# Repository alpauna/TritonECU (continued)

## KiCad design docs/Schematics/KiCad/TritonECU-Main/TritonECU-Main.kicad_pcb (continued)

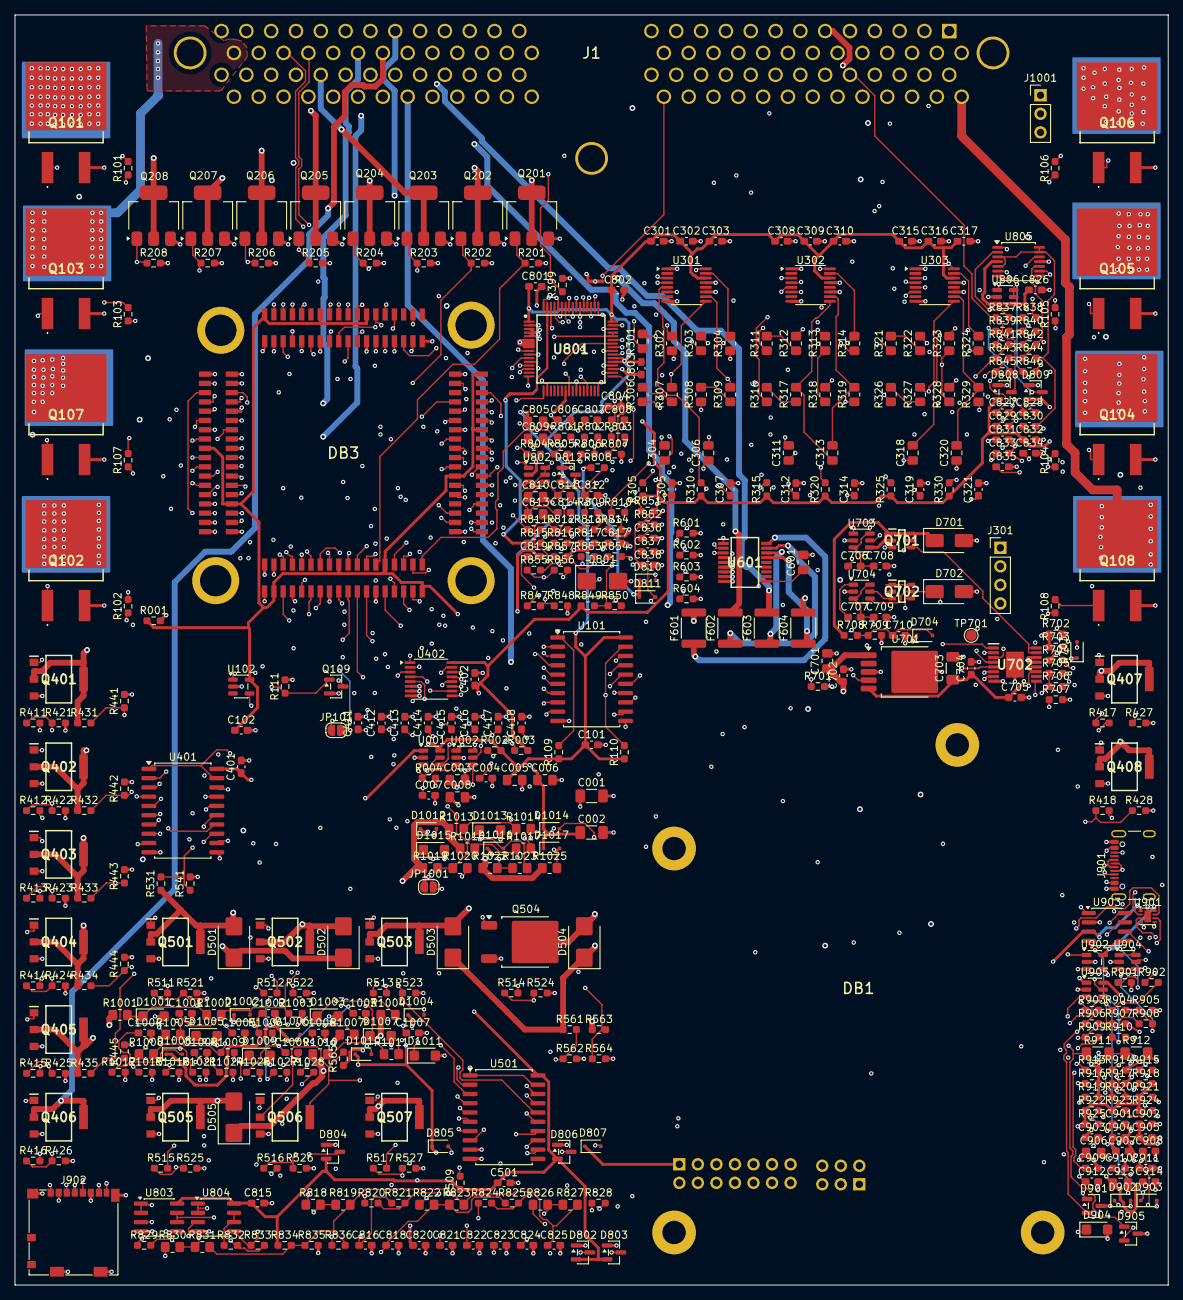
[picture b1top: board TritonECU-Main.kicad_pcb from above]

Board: 6 copper layers, 158.0 x 174.0 mm, 457 parts (0 on the bottom side), 358 nets.

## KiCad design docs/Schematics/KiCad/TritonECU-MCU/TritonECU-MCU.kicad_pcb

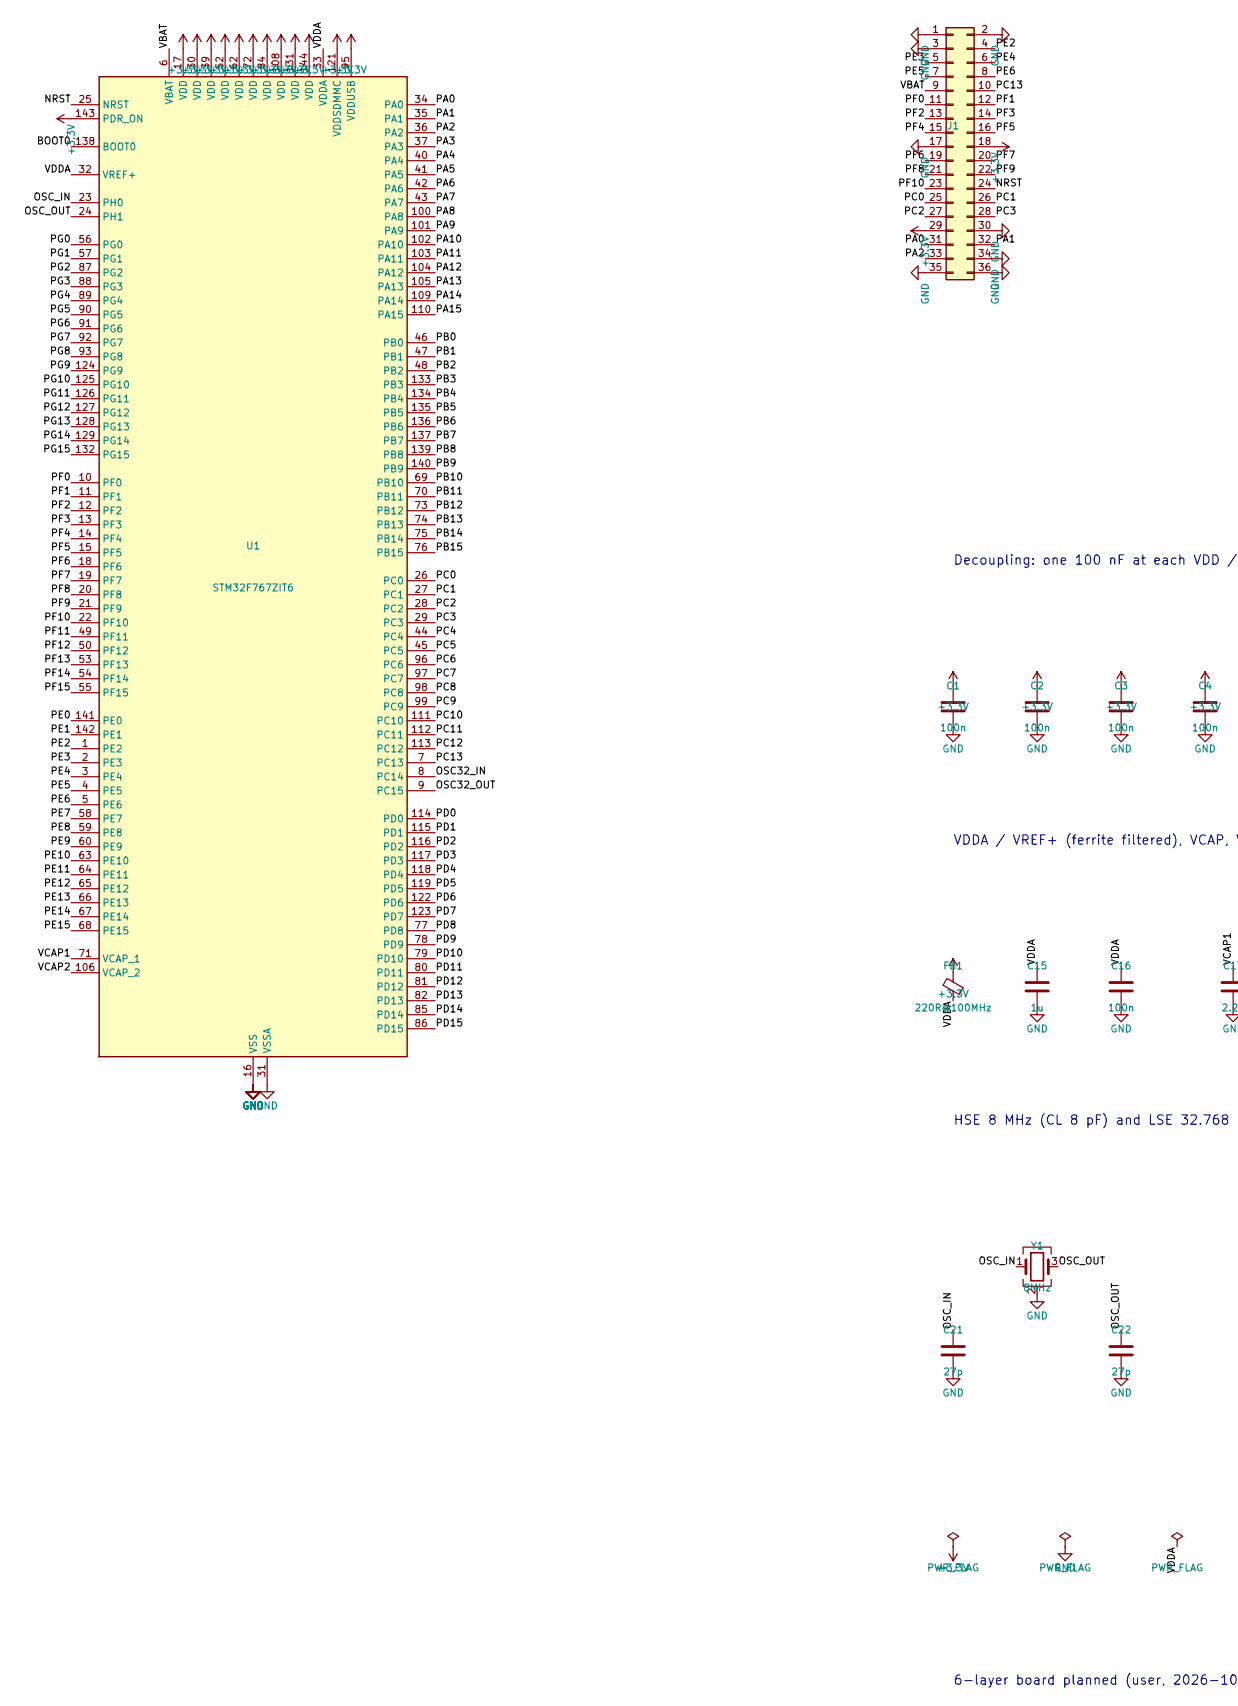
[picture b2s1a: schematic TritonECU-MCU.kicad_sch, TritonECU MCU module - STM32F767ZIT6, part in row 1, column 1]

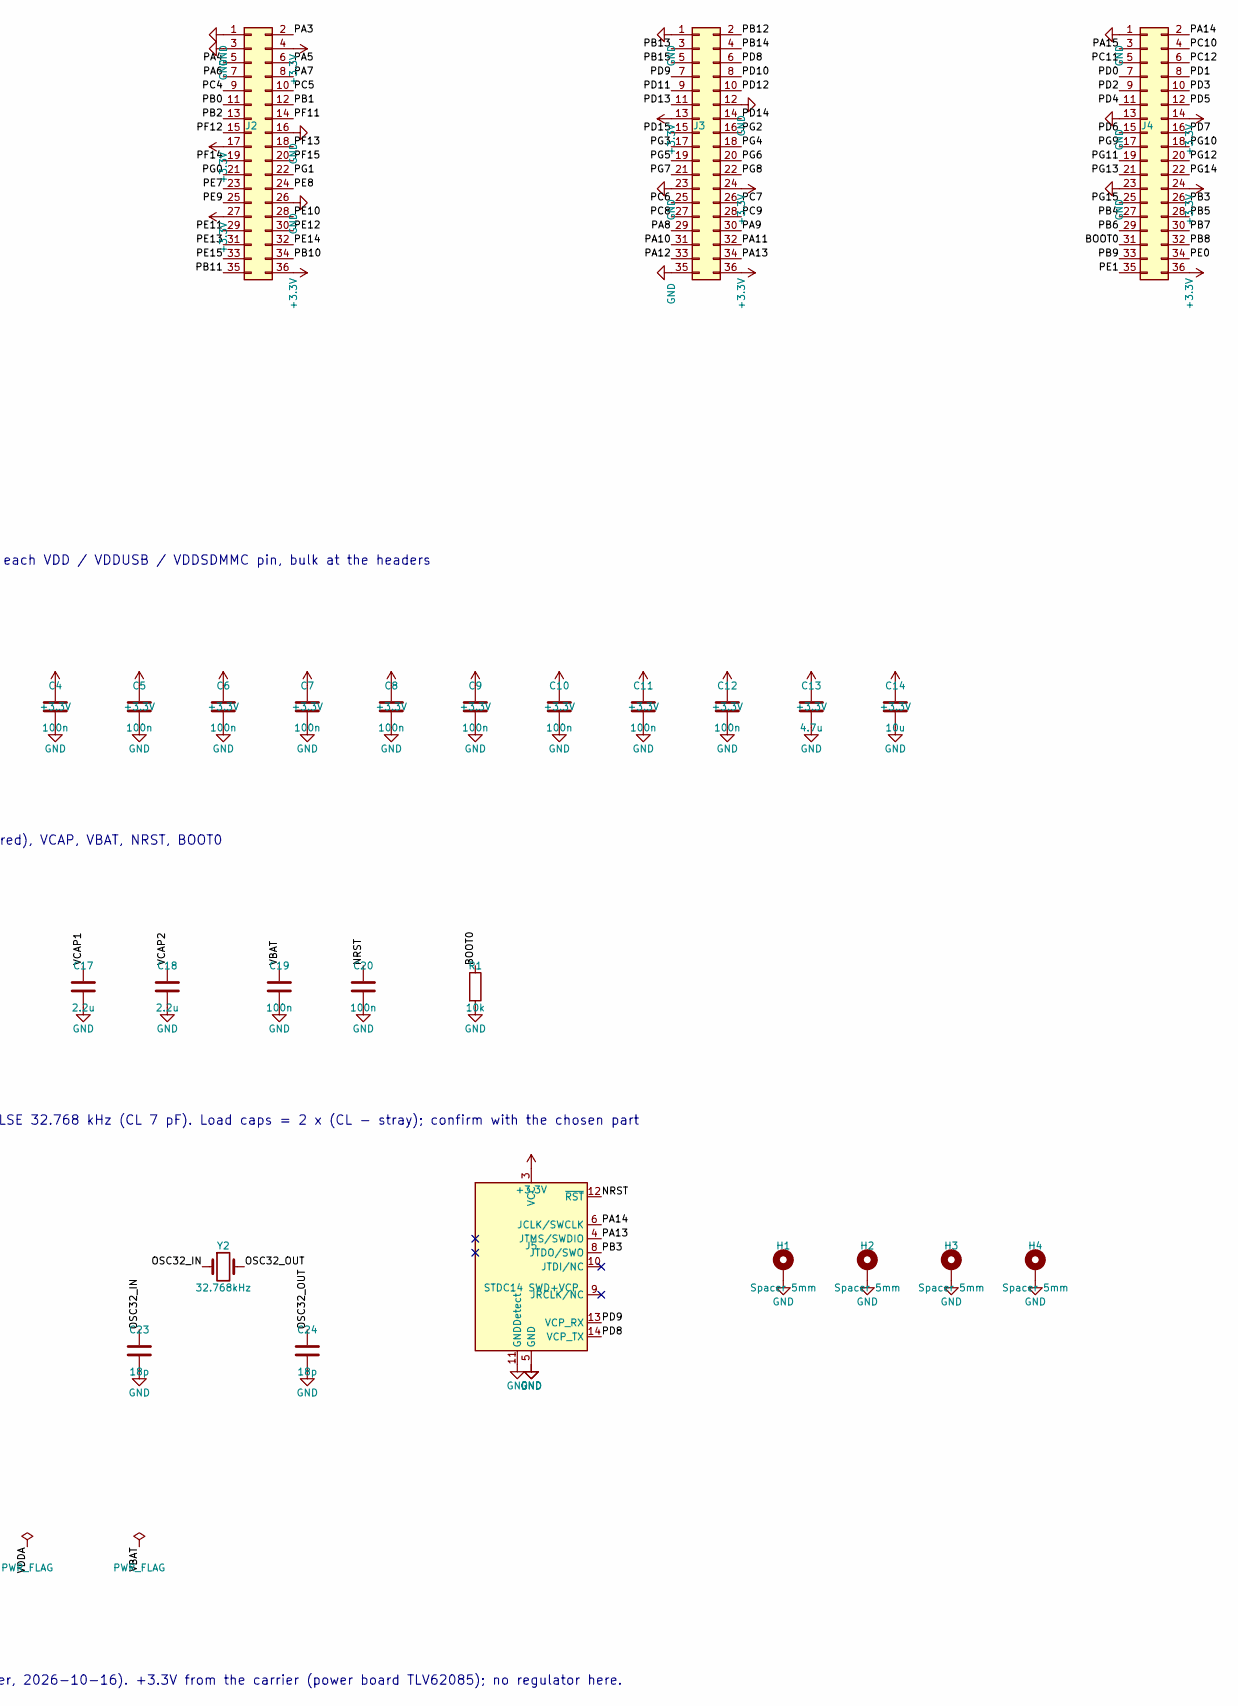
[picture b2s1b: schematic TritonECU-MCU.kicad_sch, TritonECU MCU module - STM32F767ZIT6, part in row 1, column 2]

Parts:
C1, C2, C3, C4, C5, C6, C7, C8, C9, C10, C11, C12, C16, C19, C20: 100n; C_0402_1005Metric_Pad0.74x0.62mm_HandSolder; Manufacturer_Part_Number GCM155L8EH104KE07D; Mouser Part Number 81-GCM155L8EH104KE7D
C13: 4.7u; C_0603_1608Metric_Pad1.08x0.95mm_HandSolder; Manufacturer_Part_Number GRM188C71A475ME11D; Mouser Part Number 81-GRM188C71A475ME1D
C14: 10u; C_0805_2012Metric_Pad1.18x1.45mm_HandSolder; Manufacturer_Part_Number MCASL21GBB7106KTNA01; Mouser Part Number 963-MCASL21GBB7106KT
C15: 1u; C_0402_1005Metric_Pad0.74x0.62mm_HandSolder; Manufacturer_Part_Number KAM05CR71A105KH; Mouser Part Number 581-KAM05CR71A105KH
C17, C18: 2.2u; C_0603_1608Metric_Pad1.08x0.95mm_HandSolder; Manufacturer_Part_Number KGM15BR71A225KT; Mouser Part Number 581-KGM15BR71A225KT
C21, C22: 27p; C_0402_1005Metric_Pad0.74x0.62mm_HandSolder; Mouser Part Number 80-C0402C270F4HAUTO
C23, C24: 18p; C_0402_1005Metric_Pad0.74x0.62mm_HandSolder; Mouser Part Number 603-AC0402GRNPO9BN18
FB1: 220R@100MHz; L_0603_1608Metric_Pad1.05x0.95mm_HandSolder; Manufacturer_Part_Number BBPY00201209221Y00; Mouser Part Number 603-BBPY201209221Y00
H1, H2, H3, H4: Spacer 5mm; Wurth_WA-SMST_9774050982R; MPN 9774050982R
J1, J2, J3, J4: Samtec_FTSH-118-02-L-DV-A; MPN FTSH-118-02-L-DV-A
J5: STDC14 SWD+VCP; PinHeader_2x07_P1.27mm_Vertical_SMD; MPN FTSH-107-01-L-DV-K; Mouser Part Number 200-FTSH10701LDVKATR
R1: 10k; R_0402_1005Metric_Pad0.72x0.64mm_HandSolder; Manufacturer_Part_Number AT0402FRE0710KL; Mouser Part Number 603-AT0402FRE0710KL
U1: STM32F767ZIT6; LQFP-144_20x20mm_P0.5mm; MPN STM32F767ZIT6
Y1: 8MHz; Crystal_SMD_3225-4Pin_3.2x2.5mm_HandSoldering; Mouser Part Number 815-M8AIG-8-1ZT
Y2: 32.768kHz; Crystal_SMD_2012-2Pin_2.0x1.2mm_HandSoldering; Mouser Part Number 520-.327-12.5-12QST

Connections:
+3.3V: C1.1, C2.1, C3.1, C4.1, C5.1, C6.1, C7.1, C8.1, C9.1, C10.1, C11.1, C12.1, C13.1, C14.1, FB1.1, J1.18, J1.29, J2.4, J2.17, J2.27, J2.36, J3.13, J3.24, J3.36, J4.14, J4.24, J4.36, J5.3 (VCC), U1.17 (VDD), U1.30 (VDD), U1.39 (VDD), U1.52 (VDD), U1.62 (VDD), U1.72 (VDD), U1.84 (VDD), U1.95 (VDDUSB), U1.108 (VDD), U1.121 (VDDSDMMC), U1.131 (VDD), U1.143 (PDR_ON), U1.144 (VDD)
/BOOT0: J4.31, R1.1, U1.138 (BOOT0)
/NRST: C20.1, J1.24, J5.12 (~RST), U1.25 (NRST)
/OSC32_IN: C23.1, U1.8 (PC14), Y2.1
/OSC32_OUT: C24.1, U1.9 (PC15), Y2.2
/OSC_IN: C21.1, U1.23 (PH0), Y1.1
/OSC_OUT: C22.1, U1.24 (PH1), Y1.3
/PA0: J1.31, U1.34 (PA0)
/PA1: J1.32, U1.35 (PA1)
/PA2: J1.33, U1.36 (PA2)
/PA3: J2.2, U1.37 (PA3)
/PA4: J2.5, U1.40 (PA4)
/PA5: J2.6, U1.41 (PA5)
/PA6: J2.7, U1.42 (PA6)
/PA7: J2.8, U1.43 (PA7)
/PA8: J3.29, U1.100 (PA8)
/PA9: J3.30, U1.101 (PA9)
/PA10: J3.31, U1.102 (PA10)
/PA11: J3.32, U1.103 (PA11)
/PA12: J3.33, U1.104 (PA12)
/PA13: J3.34, J5.4 (JTMS/SWDIO), U1.105 (PA13)
/PA14: J4.2, J5.6 (JCLK/SWCLK), U1.109 (PA14)
/PA15: J4.3, U1.110 (PA15)
/PB0: J2.11, U1.46 (PB0)
/PB1: J2.12, U1.47 (PB1)
/PB2: J2.13, U1.48 (PB2)
/PB3: J4.26, J5.8 (JTDO/SWO), U1.133 (PB3)
/PB4: J4.27, U1.134 (PB4)
/PB5: J4.28, U1.135 (PB5)
/PB6: J4.29, U1.136 (PB6)
/PB7: J4.30, U1.137 (PB7)
/PB8: J4.32, U1.139 (PB8)
/PB9: J4.33, U1.140 (PB9)
/PB10: J2.34, U1.69 (PB10)
/PB11: J2.35, U1.70 (PB11)
/PB12: J3.2, U1.73 (PB12)
/PB13: J3.3, U1.74 (PB13)
/PB14: J3.4, U1.75 (PB14)
/PB15: J3.5, U1.76 (PB15)
/PC0: J1.25, U1.26 (PC0)
/PC1: J1.26, U1.27 (PC1)
/PC2: J1.27, U1.28 (PC2)
/PC3: J1.28, U1.29 (PC3)
/PC4: J2.9, U1.44 (PC4)
/PC5: J2.10, U1.45 (PC5)
/PC6: J3.25, U1.96 (PC6)
/PC7: J3.26, U1.97 (PC7)
/PC8: J3.27, U1.98 (PC8)
/PC9: J3.28, U1.99 (PC9)
/PC10: J4.4, U1.111 (PC10)
/PC11: J4.5, U1.112 (PC11)
/PC12: J4.6, U1.113 (PC12)
/PC13: J1.10, U1.7 (PC13)
/PD0: J4.7, U1.114 (PD0)
/PD1: J4.8, U1.115 (PD1)
/PD2: J4.9, U1.116 (PD2)
/PD3: J4.10, U1.117 (PD3)
/PD4: J4.11, U1.118 (PD4)
/PD5: J4.12, U1.119 (PD5)
/PD6: J4.15, U1.122 (PD6)
/PD7: J4.16, U1.123 (PD7)
/PD8: J3.6, J5.14 (VCP_TX), U1.77 (PD8)
/PD9: J3.7, J5.13 (VCP_RX), U1.78 (PD9)
/PD10: J3.8, U1.79 (PD10)
/PD11: J3.9, U1.80 (PD11)
/PD12: J3.10, U1.81 (PD12)
/PD13: J3.11, U1.82 (PD13)
/PD14: J3.14, U1.85 (PD14)
/PD15: J3.15, U1.86 (PD15)
/PE0: J4.34, U1.141 (PE0)
/PE1: J4.35, U1.142 (PE1)
/PE2: J1.4, U1.1 (PE2)
/PE3: J1.5, U1.2 (PE3)
/PE4: J1.6, U1.3 (PE4)
/PE5: J1.7, U1.4 (PE5)
/PE6: J1.8, U1.5 (PE6)
/PE7: J2.23, U1.58 (PE7)
/PE8: J2.24, U1.59 (PE8)
/PE9: J2.25, U1.60 (PE9)
/PE10: J2.28, U1.63 (PE10)
/PE11: J2.29, U1.64 (PE11)
/PE12: J2.30, U1.65 (PE12)
/PE13: J2.31, U1.66 (PE13)
/PE14: J2.32, U1.67 (PE14)
/PE15: J2.33, U1.68 (PE15)
/PF0: J1.11, U1.10 (PF0)
/PF1: J1.12, U1.11 (PF1)
/PF2: J1.13, U1.12 (PF2)
/PF3: J1.14, U1.13 (PF3)
/PF4: J1.15, U1.14 (PF4)
/PF5: J1.16, U1.15 (PF5)
/PF6: J1.19, U1.18 (PF6)
/PF7: J1.20, U1.19 (PF7)
/PF8: J1.21, U1.20 (PF8)
/PF9: J1.22, U1.21 (PF9)
/PF10: J1.23, U1.22 (PF10)
/PF11: J2.14, U1.49 (PF11)
/PF12: J2.15, U1.50 (PF12)
/PF13: J2.18, U1.53 (PF13)
/PF14: J2.19, U1.54 (PF14)
/PF15: J2.20, U1.55 (PF15)
/PG0: J2.21, U1.56 (PG0)
/PG1: J2.22, U1.57 (PG1)
/PG2: J3.16, U1.87 (PG2)
/PG3: J3.17, U1.88 (PG3)
/PG4: J3.18, U1.89 (PG4)
/PG5: J3.19, U1.90 (PG5)
/PG6: J3.20, U1.91 (PG6)
/PG7: J3.21, U1.92 (PG7)
/PG8: J3.22, U1.93 (PG8)
/PG9: J4.17, U1.124 (PG9)
/PG10: J4.18, U1.125 (PG10)
/PG11: J4.19, U1.126 (PG11)
/PG12: J4.20, U1.127 (PG12)
/PG13: J4.21, U1.128 (PG13)
/PG14: J4.22, U1.129 (PG14)
/PG15: J4.25, U1.132 (PG15)
/VBAT: C19.1, J1.9, U1.6 (VBAT)
/VCAP1: C17.1, U1.71 (VCAP_1)
/VCAP2: C18.1, U1.106 (VCAP_2)
/VDDA: C15.1, C16.1, FB1.2, U1.32 (VREF+), U1.33 (VDDA)
GND: C1.2, C2.2, C3.2, C4.2, C5.2, C6.2, C7.2, C8.2, C9.2, C10.2, C11.2, C12.2, C13.2, C14.2, C15.2, C16.2, C17.2, C18.2, C19.2, C20.2, C21.2, C22.2, C23.2, C24.2, H1.1, H2.1, H3.1, H4.1, J1.1, J1.2, J1.3, J1.17, J1.30, J1.34, J1.35, J1.36, J2.1, J2.3, J2.16, J2.26, J3.1, J3.12, J3.23, J3.35, J4.1, J4.13, J4.23, J5.5 (GND), J5.7 (GND), J5.11 (GNDDetect), R1.2, U1.16 (VSS), U1.31 (VSSA), U1.38 (VSS), U1.51 (VSS), U1.61 (VSS), U1.83 (VSS), U1.94 (VSS), U1.107 (VSS), U1.120 (VSS), U1.130 (VSS), Y1.2 (G), Y1.4 (G)

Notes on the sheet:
Decoupling: one 100 nF at each VDD / VDDUSB / VDDSDMMC pin, bulk at the headers
HSE 8 MHz (CL 8 pF) and LSE 32.768 kHz (CL 7 pF). Load caps = 2 x (CL - stray); confirm with the chosen part
VDDA / VREF+ (ferrite filtered), VCAP, VBAT, NRST, BOOT0
6-layer board planned (user, 2026-10-16). +3.3V from the carrier (power board TLV62085); no regulator here.

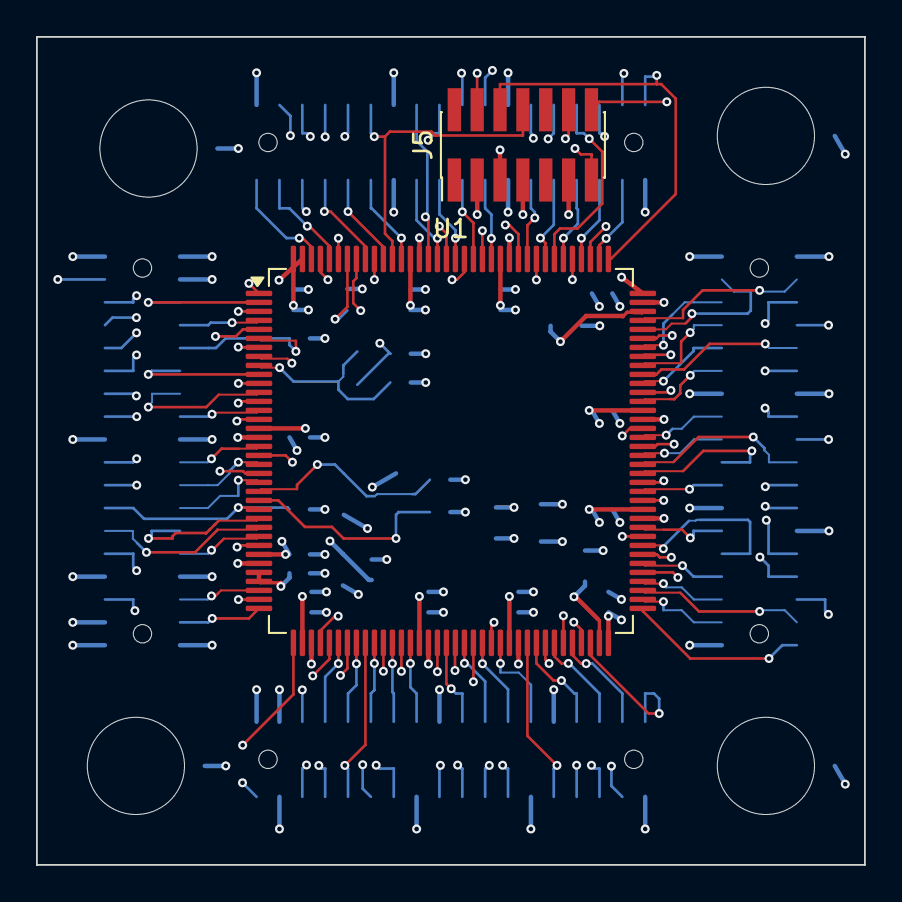
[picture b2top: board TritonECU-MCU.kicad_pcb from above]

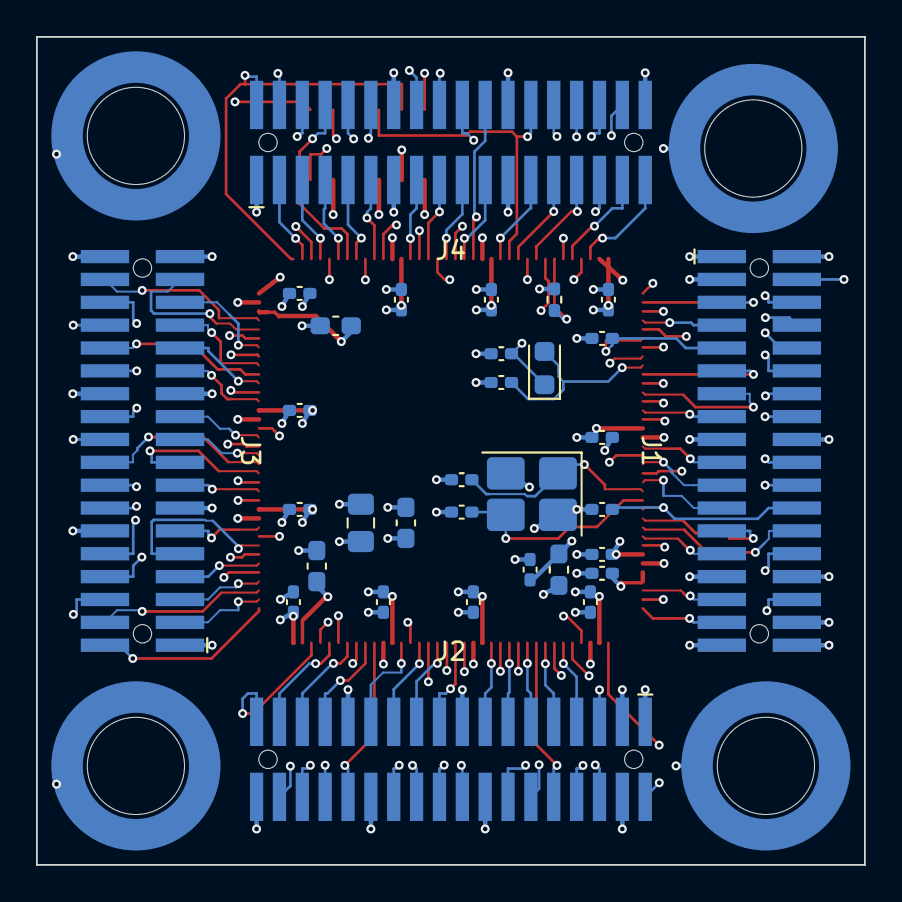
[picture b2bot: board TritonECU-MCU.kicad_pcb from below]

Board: 6 copper layers, 46.0 x 46.0 mm, 38 parts (36 on the bottom side), 122 nets.

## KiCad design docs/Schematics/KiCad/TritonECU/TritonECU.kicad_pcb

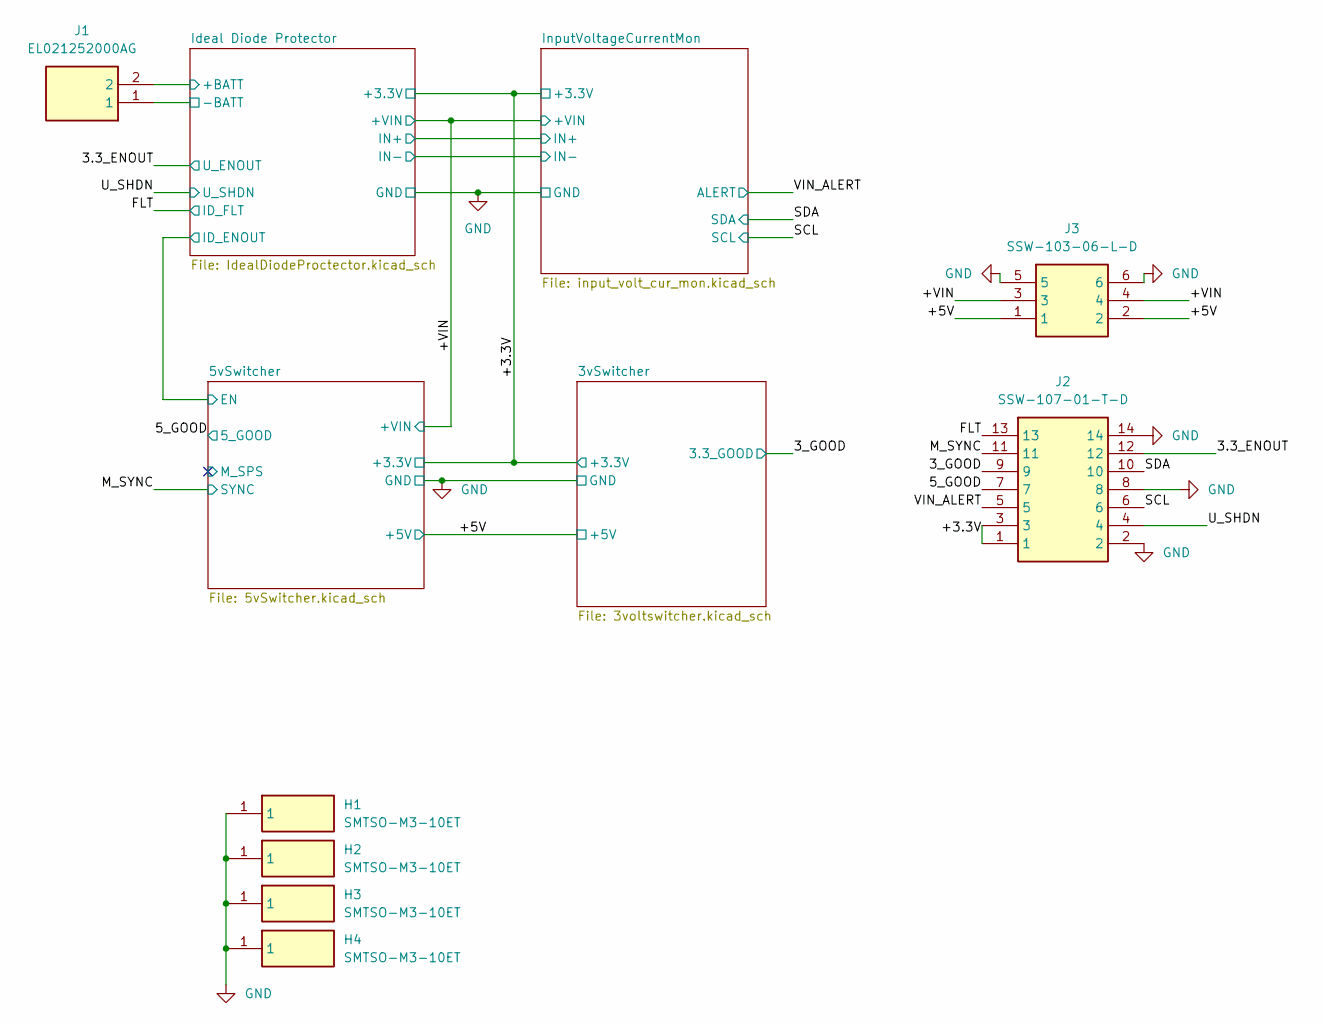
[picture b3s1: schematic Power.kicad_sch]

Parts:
H1, H2, H3, H4: SMTSO-M3-10ET; SMTSOM310ET; Manufacturer_Part_Number SMTSO-M3-10ET; Mouser Part Number 153-SMTSO-M3-10ET
J1: EL021252000AG; RHDR2W100P0X350_1X2_840X750X1130P; Manufacturer_Part_Number EL021252000AG; Mouser Part Number 523-EL021252000AG
J2: SSW-107-01-T-D; SAMTEC_SSW-107-01-T-D; Manufacturer_Part_Number SSW-107-01-T-D; Mouser Part Number 200-SSW10701TD
J3: SSW-103-06-L-D; SSW-103-XX-YYY-D; Manufacturer_Part_Number SSW-103-06-L-D; Mouser Part Number 200-SSW10306LD

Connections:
-BATT: J1.1; also elsewhere on the board
/Power/3.3_ENOUT: J2.12; also elsewhere on the board
/Power/3_GOOD: J2.9; also elsewhere on the board
/Power/5_GOOD: J2.7; also elsewhere on the board
/Power/+3.3V: J2.1, J2.3; also elsewhere on the board
/Power/+5V: J3.1, J3.2; also elsewhere on the board
/Power/+VIN: J3.3, J3.4; also elsewhere on the board
/Power/FLT: J2.13; also elsewhere on the board
/Power/Ideal Diode Protector/+BATT: J1.2; also elsewhere on the board
/Power/M_SYNC: J2.11; also elsewhere on the board
/Power/SCL: J2.6; also elsewhere on the board
/Power/SDA: J2.10; also elsewhere on the board
/Power/U_SHDN: J2.4; also elsewhere on the board
/Power/VIN_ALERT: J2.5; also elsewhere on the board
GND: H1.1 (1_1), H2.1 (1_1), H3.1 (1_1), H4.1 (1_1), J2.2, J2.8, J2.14, J3.5, J3.6; also elsewhere on the board

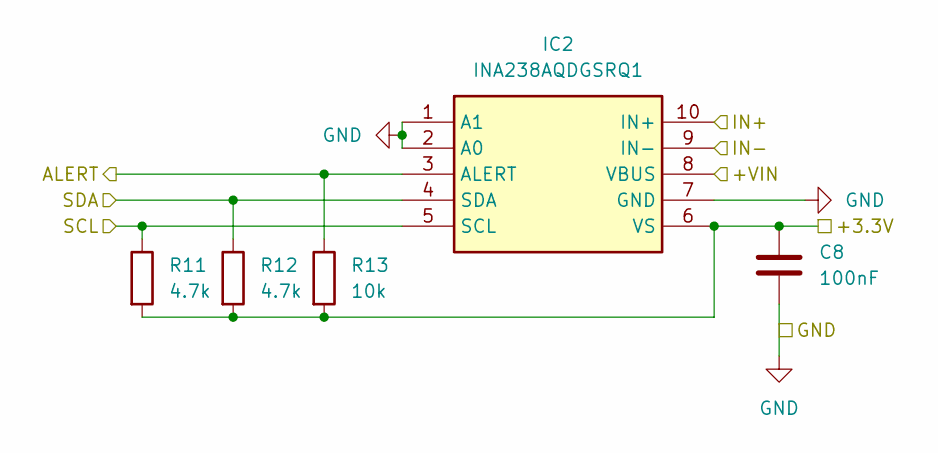
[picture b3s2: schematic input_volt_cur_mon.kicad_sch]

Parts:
C8: 100nF; C_0402_1005Metric_Pad0.74x0.62mm_HandSolder; Mouser Part Number 963-MASL105SB7104MF
IC2: INA238AQDGSRQ1; SOP50P490X110-10N; Manufacturer_Part_Number INA238AQDGSRQ1; Mouser Part Number 595-INA238AQDGSRQ1
R11, R12: 4.7k; R_0402_1005Metric_Pad0.72x0.64mm_HandSolder; Mouser Part Number 791-RMC1/16S-472JTH
R13: 10k; R_0402_1005Metric_Pad0.72x0.64mm_HandSolder; Mouser Part Number 652-CRT0402BY1002GLF

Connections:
/Power/+3.3V: C8.1, IC2.6 (VS), R11.2, R12.2, R13.2; also elsewhere on the board
/Power/+VIN: IC2.8 (VBUS), IC2.9 (IN-); also elsewhere on the board
/Power/Ideal Diode Protector/IN+: IC2.10 (IN+); also elsewhere on the board
/Power/SCL: IC2.5 (SCL), R11.1; also elsewhere on the board
/Power/SDA: IC2.4 (SDA), R12.1; also elsewhere on the board
/Power/VIN_ALERT: IC2.3 (ALERT), R13.1; also elsewhere on the board
GND: C8.2, IC2.1 (A1), IC2.2 (A0), IC2.7 (GND); also elsewhere on the board

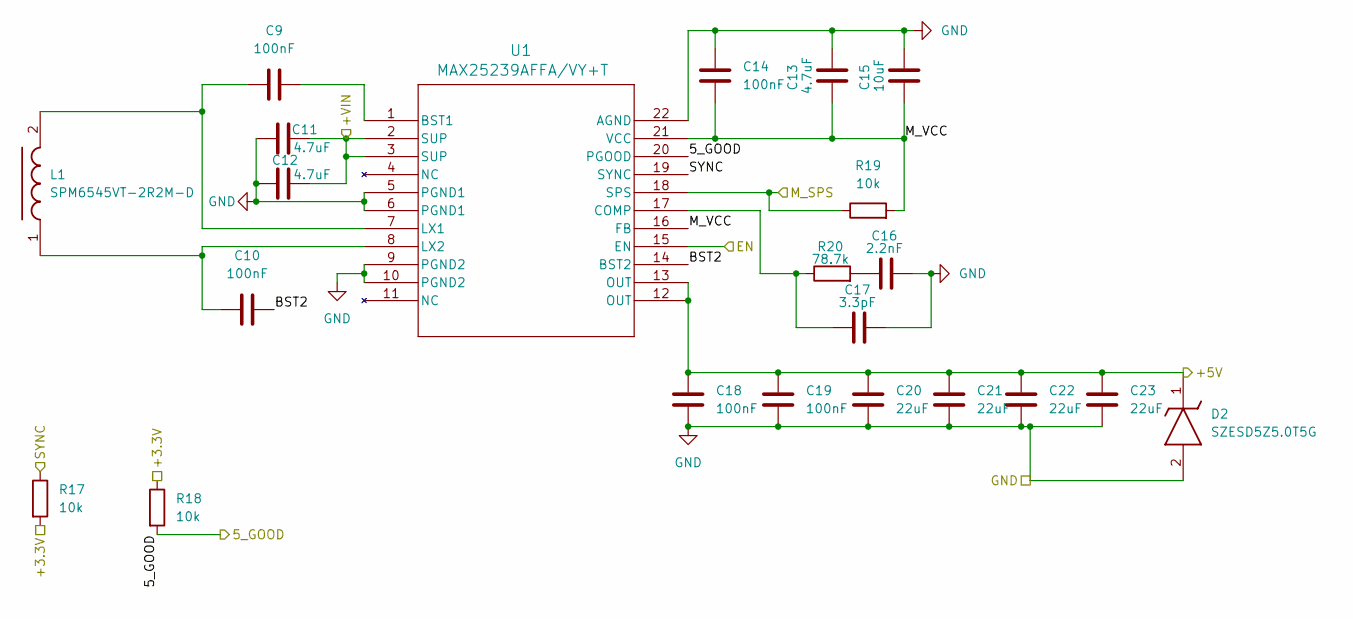
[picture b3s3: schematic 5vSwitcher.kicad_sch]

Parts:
C9, C10, C14, C18, C19: 100nF; C_0402_1005Metric_Pad0.74x0.62mm_HandSolder; Mouser Part Number 810-CGA2B3X7R1H104BD
C11, C12: 4.7uF; C_0805_2012Metric_Pad1.18x1.45mm_HandSolder; Mouser Part Number 81-GRM21BZ7YA475KE5K
C13: 4.7uF; C_0603_1608Metric_Pad1.08x0.95mm_HandSolder; Mouser Part Number 81-GRM188Z71A475ME5J
C15: 10uF; C_0805_2012Metric_Pad1.18x1.45mm_HandSolder; Mouser Part Number 581-0805YC106MAT2A
C16: 2.2nF; C_0402_1005Metric_Pad0.74x0.62mm_HandSolder; Mouser Part Number 81-GRM1555C1H222J01D
C17: 3.3pF; C_0402_1005Metric_Pad0.74x0.62mm_HandSolder; Mouser Part Number 81-GCM1555C2A3R3BE2D
C20, C21, C22, C23: 22uF; C_1206_3216Metric_Pad1.33x1.80mm_HandSolder; Mouser Part Number 963-EMK316BB7226ML-T
D2: SZESD5Z5.0T5G; SODFL1608X70N; Manufacturer_Part_Number SZESD5Z5.0T5G; Mouser Part Number 863-SZESD5Z5.0T5G
L1: SPM6545VT-2R2M-D; SPM6545VT; Manufacturer_Part_Number SPM6545VT-2R2M-D; Mouser Part Number 810-SPM6545VT-2R2M-D
R17, R18, R19: 10k; R_0402_1005Metric_Pad0.72x0.64mm_HandSolder; Mouser Part Number 652-CRT0402BY1002GLF
R20: 78.7k; R_0402_1005Metric_Pad0.72x0.64mm_HandSolder; Mouser Part Number 754-RG1005P-7872DT10
U1: MAX25239AFFA/VY+T; 21-100399_90-100137_ADI; Mouser Part Number 700-MAX25239AFFA/VY+

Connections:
/Power/5_GOOD: R18.2, U1.20 (PGOOD); also elsewhere on the board
/Power/5vSwitcher/BST2: C10.2, U1.14 (BST2)
/Power/5vSwitcher/M_SPS: R19.1, U1.18 (SPS)
/Power/5vSwitcher/M_VCC: C13.1, C14.1, C15.1, R19.2, U1.16 (FB), U1.21 (VCC)
/Power/+3.3V: R17.2, R18.1; also elsewhere on the board
/Power/+5V: C18.2, C19.2, C20.2, C21.2, C22.2, C23.2, D2.1 (K), U1.12 (OUT), U1.13 (OUT); also elsewhere on the board
/Power/+VIN: C11.2, C12.2, U1.2 (SUP), U1.3 (SUP); also elsewhere on the board
/Power/Ideal Diode Protector/ID_ENOUT: U1.15 (EN); also elsewhere on the board
/Power/M_SYNC: R17.1, U1.19 (SYNC); also elsewhere on the board
GND: C11.1, C12.1, C13.2, C14.2, C15.2, C16.1, C17.1, C18.1, C19.1, C20.1, C21.1, C22.1, C23.1, D2.2 (A), U1.5 (PGND1), U1.6 (PGND1), U1.9 (PGND2), U1.10 (PGND2), U1.22 (AGND); also elsewhere on the board
unnamed: C16.2, R20.2
unnamed: C9.2, U1.1 (BST1)
unnamed: C17.2, R20.1, U1.17 (COMP)
unnamed: C9.1, L1.2, U1.7 (LX1)
unnamed: C10.1, L1.1, U1.8 (LX2)

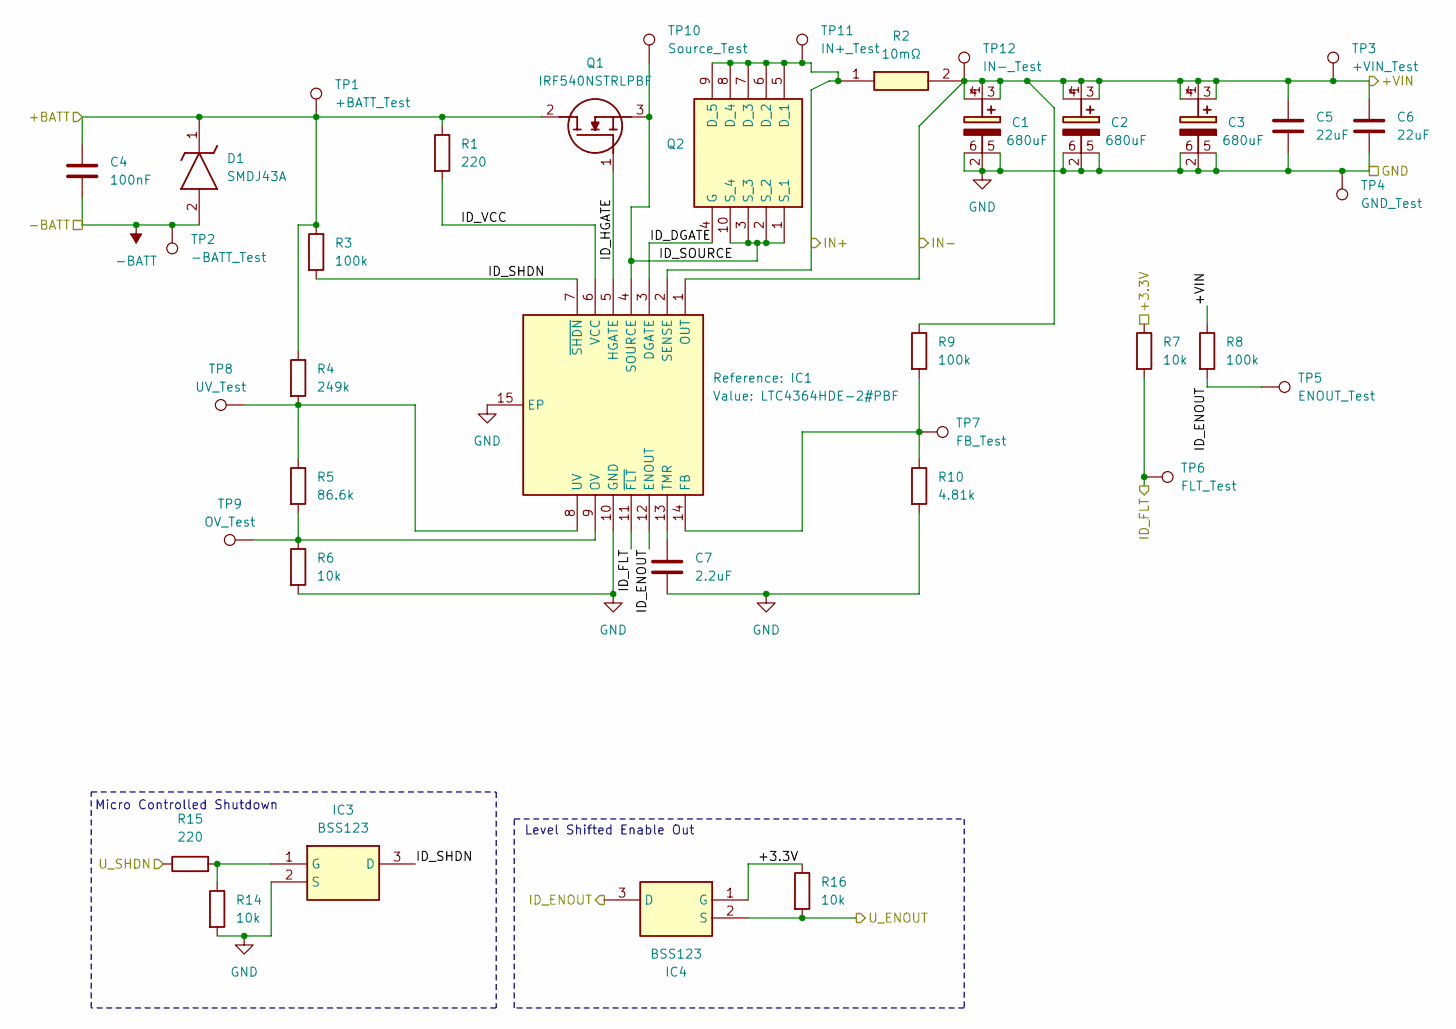
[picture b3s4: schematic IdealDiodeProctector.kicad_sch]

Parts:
C1, C2, C3: 680uF; EEHZU1E102UV; Mouser Part Number 667-EEH-ZU1V681UV
C4: 100nF; C_1808_4520Metric_Pad1.72x2.30mm_HandSolder; Mouser Part Number 77-VJ1808Y104KXCAT
C5, C6: 22uF; C_1210_3225Metric_Pad1.33x2.70mm_HandSolder; Mouser Part Number 187-CL32B226KLV6PNE
C7: 2.2uF; C_0603_1608Metric_Pad1.08x0.95mm_HandSolder; Mouser Part Number 81-GRM188Z71C225KE3D
D1: SMDJ43A; DIOM7959X262N; Mouser Part Number 652-5.0SMDJ43A
IC1: LTC4364HDE-2#PBF; SON50P300X400X80-15N-D; Mouser Part Number 584-LTC4364HDE-2#PBF
IC3, IC4: BSS123; SOT95P230X110-3N; Manufacturer_Part_Number BSS123; Mouser Part Number 512-BSS123
Q1: IRF540NSTRLPBF; IRF2804STRLPBF; Mouser Part Number 942-IRF540NSTRLPBF
Q2: IAUZ40N10S5N130ATMA1; Mouser Part Number 726-IAUZ40N10S5N130A
R1, R15: 220; R_0402_1005Metric_Pad0.72x0.64mm_HandSolder; Mouser Part Number 603-RT0402BRE07220RL
R2: 10mΩ; RESC6432X90N; Mouser Part Number 279-TLRP3A20WR010FTE
R3, R8, R9: 100k; R_0402_1005Metric_Pad0.72x0.64mm_HandSolder; Mouser Part Number 603-RC0402JR-7D100KL
R4: 249k; R_0402_1005Metric_Pad0.72x0.64mm_HandSolder; Mouser Part Number 279-RP73PF1E249KBTDF
R5: 86.6k; R_0402_1005Metric_Pad0.72x0.64mm_HandSolder; Mouser Part Number 667-ERJ-2RHD8662X
R6, R7, R14, R16: 10k; R_0402_1005Metric_Pad0.72x0.64mm_HandSolder; Mouser Part Number 652-CRT0402BY1002GLF
R10: 4.81k; R_0402_1005Metric_Pad0.72x0.64mm_HandSolder; Mouser Part Number 603-RT0402BRD074K81L
TP1: +BATT_Test; TestPoint_Pad_D1.5mm
TP2: -BATT_Test; TestPoint_Pad_D1.5mm
TP3: +VIN_Test; TestPoint_Pad_D1.5mm
TP4: GND_Test; TestPoint_Pad_D1.5mm
TP5: ENOUT_Test; TestPoint_Pad_D1.5mm
TP6: FLT_Test; TestPoint_Pad_D1.5mm
TP7: FB_Test; TestPoint_Pad_D1.5mm
TP8: UV_Test; TestPoint_Pad_D1.5mm
TP9: OV_Test; TestPoint_Pad_D1.5mm
TP10: Source_Test; TestPoint_Pad_D1.5mm
TP11: IN+_Test; TestPoint_Pad_D1.5mm
TP12: IN-_Test; TestPoint_Pad_D1.5mm

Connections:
-BATT: C4.2, D1.2 (A), TP2.1 (1_1); also elsewhere on the board
/Power/3.3_ENOUT: IC4.2 (S), R16.2; also elsewhere on the board
/Power/+3.3V: IC4.1 (G), R7.1, R16.1; also elsewhere on the board
/Power/+VIN: C1.1 (+_1), C1.3 (+_2), C1.4 (+_3), C2.1 (+_1), C2.3 (+_2), C2.4 (+_3), C3.1 (+_1), C3.3 (+_2), C3.4 (+_3), C5.1, C6.1, IC1.1 (OUT), R2.2, R8.1, R9.1, TP3.1 (1_1), TP12.1 (1_1); also elsewhere on the board
/Power/FLT: IC1.11 (~FLT), R7.2, TP6.1 (1_1); also elsewhere on the board
/Power/Ideal Diode Protector/+BATT: C4.1, D1.1 (K), Q1.2 (D), R1.1, R3.1, R4.1, TP1.1 (1_1); also elsewhere on the board
/Power/Ideal Diode Protector/ID_DGATE: IC1.3 (DGATE), Q2.4 (G)
/Power/Ideal Diode Protector/ID_ENOUT: IC1.12 (ENOUT), IC4.3 (D), R8.2, TP5.1 (1_1); also elsewhere on the board
/Power/Ideal Diode Protector/ID_HGATE: IC1.5 (HGATE), Q1.1 (G)
/Power/Ideal Diode Protector/ID_SHDN: IC1.7 (~SHDN), IC3.3 (D), R3.2
/Power/Ideal Diode Protector/ID_SOURCE: IC1.4 (SOURCE), Q1.3 (S), Q2.1 (S_1), Q2.2 (S_2), Q2.3 (S_3), Q2.10 (S_4), TP10.1 (1_1)
/Power/Ideal Diode Protector/ID_VCC: IC1.6 (VCC), R1.2
/Power/Ideal Diode Protector/IN+: IC1.2 (SENSE), Q2.5 (D_1), Q2.6 (D_2), Q2.7 (D_3), Q2.8 (D_4), Q2.9 (D_5), R2.1, TP11.1 (1_1); also elsewhere on the board
/Power/U_SHDN: R15.1; also elsewhere on the board
GND: C1.2 (-_1), C1.5 (-_2), C1.6 (-_3), C2.2 (-_1), C2.5 (-_2), C2.6 (-_3), C3.2 (-_1), C3.5 (-_2), C3.6 (-_3), C5.2, C6.2, C7.2, IC1.10 (GND), IC1.15 (EP), IC3.2 (S), R6.2, R10.2, R14.2, TP4.1 (1_1); also elsewhere on the board
unnamed: IC1.14 (FB), R9.2, R10.1, TP7.1 (1_1)
unnamed: IC1.9 (OV), R5.2, R6.1, TP9.1 (1_1)
unnamed: C7.1, IC1.13 (TMR)
unnamed: IC1.8 (UV), R4.2, R5.1, TP8.1 (1_1)
unnamed: IC3.1 (G), R14.1, R15.2

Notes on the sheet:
Micro Controlled Shutdown
Level Shifted Enable Out

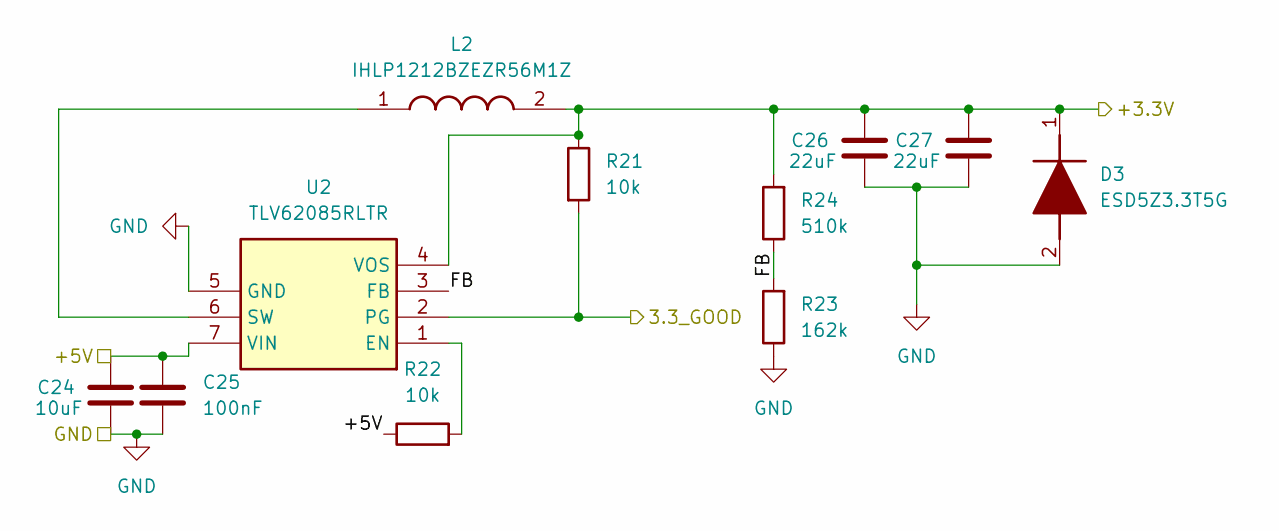
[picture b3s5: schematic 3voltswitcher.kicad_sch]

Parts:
C24: 10uF; C_0805_2012Metric_Pad1.18x1.45mm_HandSolder; Mouser Part Number 581-0805YC106MAT2A
C25: 100nF; C_0402_1005Metric_Pad0.74x0.62mm_HandSolder; Mouser Part Number 810-CGA2B3X7R1H104BD
C26, C27: 22uF; C_1206_3216Metric_Pad1.33x1.80mm_HandSolder; Mouser Part Number 963-MAASL31LAB7226MT
D3: ESD5Z3.3T5G; SODFL1608X70N; Manufacturer_Part_Number ESD5Z3.3T5G; Mouser Part Number 863-ESD5Z3.3T5G
L2: IHLP1212BZEZR56M1Z; Manufacturer_Part_Number IHLP1212BZEZR56M1Z; Mouser Part Number 70-IHLP1212BZEZR56M
R21, R22: 10k; R_0402_1005Metric_Pad0.72x0.64mm_HandSolder; Mouser Part Number 652-CRT0402BY1002GLF
R23: 162k; R_0402_1005Metric_Pad0.72x0.64mm_HandSolder; Mouser Part Number 603-RC0402DR-07162KL
R24: 510k; R_0402_1005Metric_Pad0.72x0.64mm_HandSolder; Mouser Part Number 667-ERJ-2RKD5103X
U2: TLV62085RLTR; RLT0007A; Manufacturer_Part_Number TLV62085RLTR; Mouser Part Number 595-TLV62085RLTR

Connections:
/Power/3_GOOD: R21.2, U2.2 (PG); also elsewhere on the board
/Power/3vSwitcher/FB: R23.2, R24.1, U2.3 (FB)
/Power/+3.3V: C26.2, C27.2, D3.1 (K), L2.2, R21.1, R24.2, U2.4 (VOS); also elsewhere on the board
/Power/+5V: C24.2, C25.2, R22.1, U2.7 (VIN); also elsewhere on the board
GND: C24.1, C25.1, C26.1, C27.1, D3.2 (A), R23.1, U2.5 (GND); also elsewhere on the board
unnamed: R22.2, U2.1 (EN)
unnamed: L2.1, U2.6 (SW)
